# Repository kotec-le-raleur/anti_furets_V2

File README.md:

# anti_furets_V2
##  Anti_furets V2, avec plus de trucs super extra méga cools

* liste des ajouts:
  * un montage plus astucieux pour commander le HP Piézo ( genre de push-pull)
  * un opto-coupleur et triac  8A pour commander une grosse lampe ( coupure au zéro secteur avec un MOC3041)
  * un fusible sur le 12V
  * une carte 80X40 mm faite chez JLCPCB . Le luxe !

Dispositif générateur d'ultra-sons et de flashs lumineux pour effrayer les nuisibles dans un grenier

Ce petit montage trivial , garanti sans NE555, génére des suites aléatoires de sons dans la gamme des 15 à 22 kilo Hertz.   
Des flashs lumineux peuvent être ajoutés avec une ampoule LED 12V ou un ruban de leds.    
On peut aussi mettre un relais pour augmenter la puissance, mais il faudra que la charge et le relais supportent les marche/arret sans griller.   
La consommation sans l'ampoule LED est de 50 mA et une prise murale alim 12V suffit largement !   
Si une diode zéner est utilisée à la place du régulateur, vérifier que la tension à ses bornes ne dépasse pas 5V avant de plugger le µcontrôleur. 

Il faut penser à installer le core ATTiny85 qui implémente la fonction Tone() avant de compiler/télécharger le programme Ajouter dans le menu de l'IDE Arduino la ligne : http://drazzy.com/package_drazzy.com_index.json

Test en vrai: j'ai deux montages comme celui-là dans mon grenier depuis 2 ans !  
il faut bien le placer dans le chemin emprunté par les furets (ou fouines )  
J'ai ajouté des cubes de déodorants pour WC dans les passages et deux diffuseurs ambi-pur océan  (les plus puants )  
Ces saloperies de bestioles se sont barrés pour l'instant , mais la guerre contibue ....  
Bientôt les pièges électriques et mortels !  

A suivre

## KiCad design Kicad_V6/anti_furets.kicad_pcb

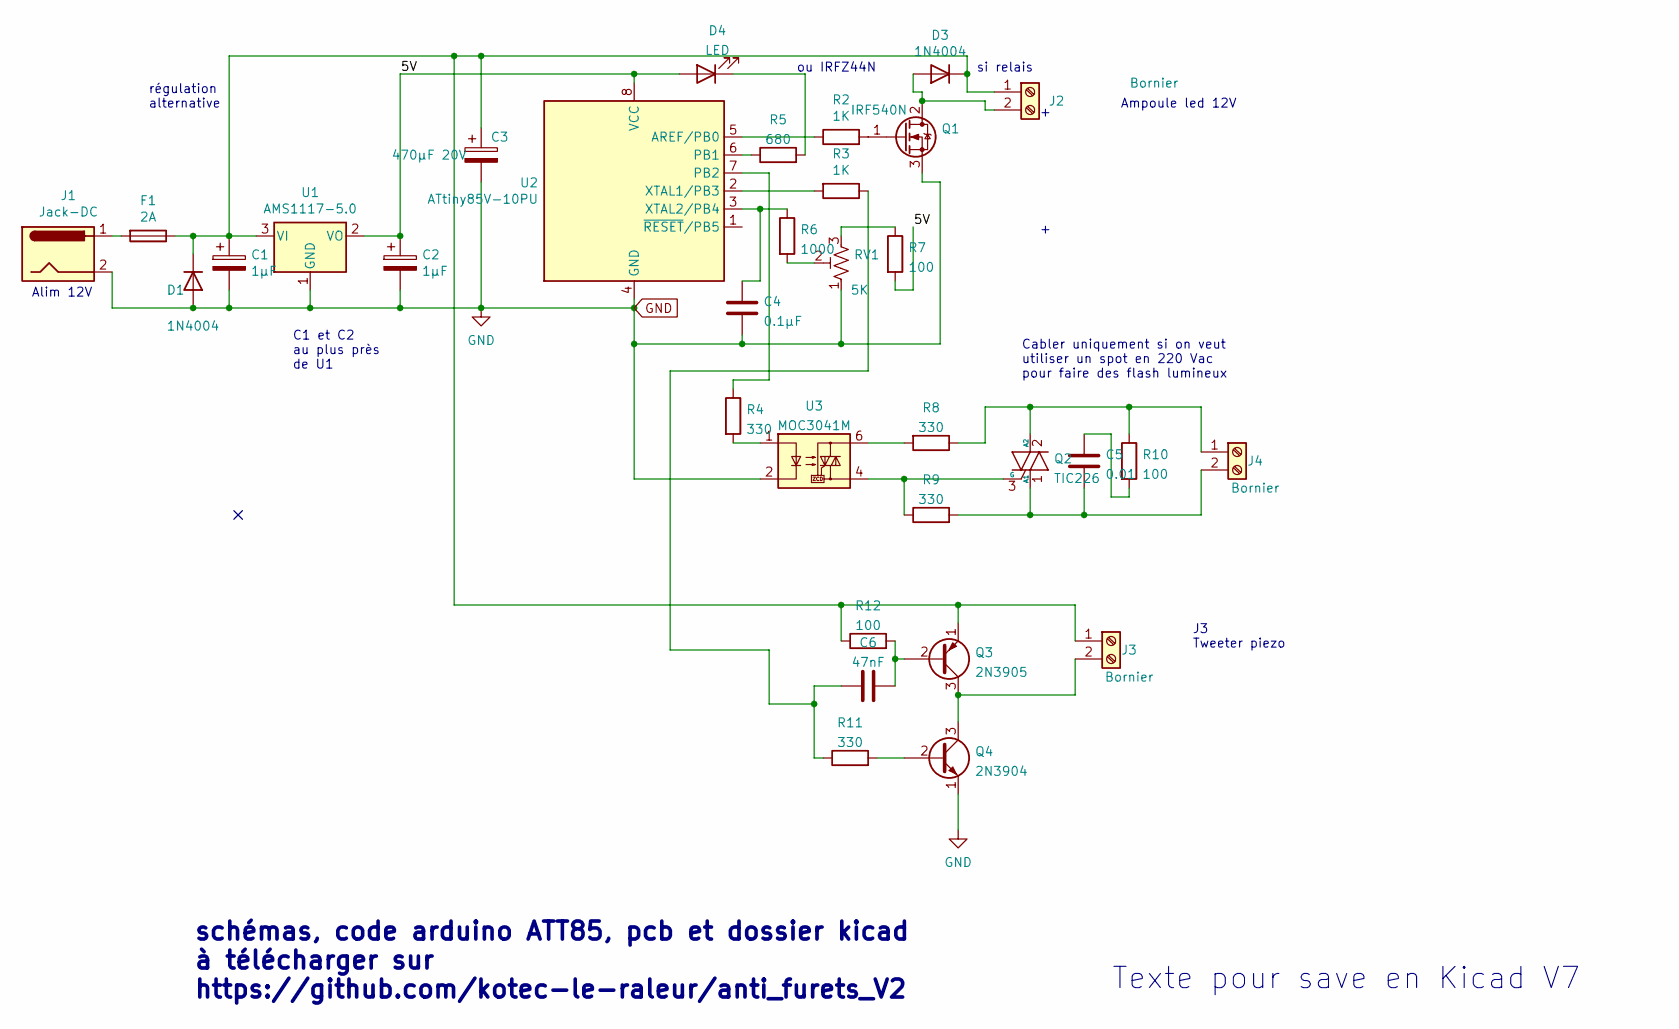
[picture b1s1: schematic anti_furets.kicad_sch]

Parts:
C1, C2: 1µF; C_1206_3216Metric_Pad1.33x1.80mm_HandSolder
C3: 470µF 20V; CP_Radial_D10.0mm_P5.00mm
C4: 0.1µF; C_1210_3225Metric_Pad1.33x2.70mm_HandSolder
C5: 0.01; C_Rect_L7.0mm_W2.0mm_P5.00mm
C6: 47nF; C_Rect_L7.0mm_W2.0mm_P5.00mm
D1, D3: 1N4004; D_DO-41_SOD81_P10.16mm_Horizontal
D4: LED; LED_2010_5025Metric_Pad1.52x2.65mm_HandSolder
F1: 2A; Fuseholder_Littelfuse_445_030_series_5x20mm
J1: Jack-DC; BarrelJack_Wuerth_6941xx301002
J2, J3, J4: Bornier; PinHeader_1x03_P2.54mm_Vertical
Q1: IRF540N; TO-220-3_Vertical
Q2: TIC226; TO-220-3_Vertical
Q3: 2N3905; TO-92_Inline
Q4: 2N3904; TO-92_Inline
R2, R3: 1K; R_0805_2012Metric_Pad1.20x1.40mm_HandSolder
R4, R11: 330; R_0805_2012Metric_Pad1.20x1.40mm_HandSolder
R5: 680; R_0805_2012Metric_Pad1.20x1.40mm_HandSolder
R6: 1000; R_0805_2012Metric_Pad1.20x1.40mm_HandSolder
R7, R12: 100; R_0805_2012Metric_Pad1.20x1.40mm_HandSolder
R8, R9: 330; R_Axial_DIN0207_L6.3mm_D2.5mm_P10.16mm_Horizontal
R10: 100; R_Axial_DIN0207_L6.3mm_D2.5mm_P10.16mm_Horizontal
RV1: 5K; Potentiometer_ACP_CA9-H3,8_Horizontal
U1: AMS1117-5.0; SOT-223-3_TabPin2
U2: ATtiny85V-10PU; DIP-8_W10.16mm_LongPads
U3: MOC3041M; DIP-6_W10.16mm_LongPads

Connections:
/5V: C2.1, D4.2 (A), R7.2, U1.2 (VO), U2.8 (VCC)
GND: C1.2, C2.2, C3.2, C4.2, D1.2 (A), J1.2, Q1.3 (S), Q4.1 (E), RV1.1, U1.1 (GND), U2.4 (GND), U3.2
unnamed: C1.1, C3.1, D1.1 (K), D3.1 (K), F1.1, J2.1, J3.1, Q3.1 (E), R12.1, U1.3 (VI)
unnamed: C4.1, R6.1, U2.3 (XTAL2/PB4)
unnamed: C5.1, R10.2
unnamed: C5.2, J4.2, J4.3, Q2.1 (A1), R9.2
unnamed: C6.1, R3.1, R11.1
unnamed: C6.2, Q3.2 (B), R12.2
unnamed: D3.2 (A), J2.2, J2.3, Q1.2 (D)
unnamed: D4.1 (K), R5.2
unnamed: F1.2, J1.1
unnamed: J3.2, J3.3, Q3.3 (C), Q4.3 (C)
unnamed: J4.1, Q2.2 (A2), R8.1, R10.1
unnamed: Q1.1 (G), R2.2
unnamed: Q2.3 (G), R9.1, U3.4
unnamed: Q4.2 (B), R11.2
unnamed: R2.1, U2.5 (AREF/PB0)
unnamed: R3.2, U2.2 (XTAL1/PB3)
unnamed: R4.1, U2.7 (PB2)
unnamed: R4.2, U3.1
unnamed: R5.1, U2.6 (PB1)
unnamed: R6.2, RV1.2
unnamed: R7.1, RV1.3
unnamed: R8.2, U3.6

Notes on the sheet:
Alim 12V
C1 et C2 au plus près de U1
Cabler uniquement si on veut utiliser un spot en 220 Vac pour faire des flash lumineux
schémas, code arduino ATT85, pcb et dossier kicad à télécharger sur https://github.com/kotec-le-raleur/anti_furets_V2
si relais
ou IRFZ44N
Texte pour save en Kicad V7
régulation alternative
J3 Tweeter piezo
Ampoule led 12V

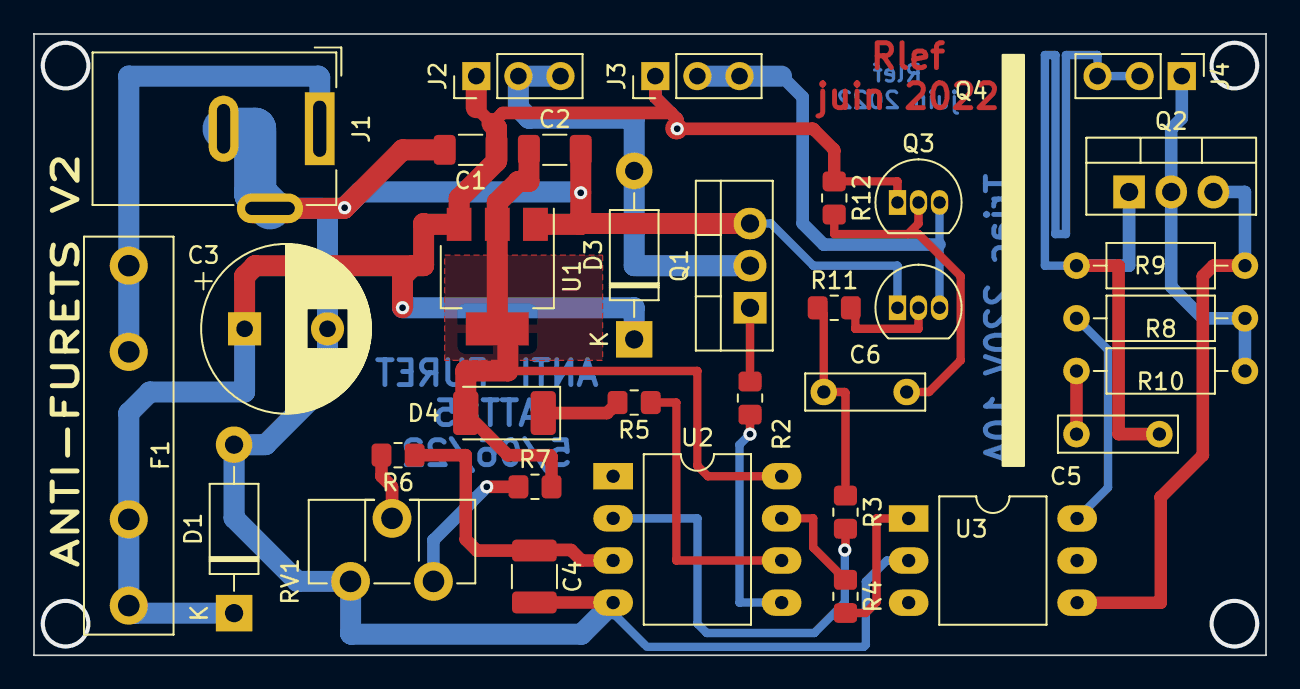
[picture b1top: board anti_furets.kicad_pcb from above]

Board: 2 copper layers, 74.3 x 37.5 mm, 33 parts (0 on the bottom side), 24 nets.

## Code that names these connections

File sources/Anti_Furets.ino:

//  René Lefebvre 6 decembre 2020

// programme chasse_furet
// Pour éloigner cette merde qui squatte le grenier (et qui chie partout)
// Un bon paquet d'ultra-son entre 13 kHz et 18 kHz (à la louche)
// en mode rafale aléatoire
// plus des flashs lumineux aléatoires eux aussi

// ATTENTION  la fonction tone() ne fonctionne pas avec tous les cores att85
// il faut installer le core suivant: http://drazzy.com/package_drazzy.com_index.json
//
// PINS    ATT85
//        ________U_______
//        | 1:RST  8: Vcc |
//        | 2:PB3  7: PB2 | 
//        | 3:PB4  6: PB1 | 
//        | 4:Gnd  5: PB0 | 
//        -----------------


  
    // PB5----pin 1 0 pin 8----Vcc
// A3  PB3----pin 2   pin 7----PB2 A1
// A2  PB4----pin 3   pin 6----PB1
    // Gnd----pin 4   pin 5----PB0
 
//  la tension lue sur A3 est convertie en valeur entre 0 et 1023
//  on multiple par 15 et cela sert de minimum pour la fréquence
//  quand on n'entend plus rien c'est que on est au choix : 
//					sourd, 
//					agé de plus de 60 ans, 
//					ou dans la gamme des ultra sons !
//
// mes chats ont bougé la tête à 20 m du HP, donc , ça fonctionne 
 
 
#define OUT_PIN PB4     // pin 3    vers la gate du 2N7000 pour le HP
#define AJUST_PIN PB3   // pin 2	vers le curseur du potentiometre  0..5V
#define LAMPE_PIN PB0   // pin 5    vers la gate du  IRFZ44 pour le spot

#define NB_FREQ 25

// les fréquences à zéro allument le spot lumineux
int Tab_FREQ[NB_FREQ]  = {100,200,345,0,550,700,850,0,952,1050,1250,1777,
                          1954,0,2154,2500,2750,3000,3300,0,3700,4050,4500,4990,0};
						  
int Tab_SILENCE[10]    = {20,50,80,100,250,300,450,500,750,800};
int Base = 10;     // Initialisation

//*******************  MAIN   *********************
void setup() {
  pinMode(OUT_PIN, OUTPUT);
  pinMode(LAMPE_PIN, OUTPUT);
 //Initialisation du random avec la clé universelle
  randomSeed(42);     
}

//*******************  LOOP   *********************
void loop() {
int i=0;
long frq, tp;
for (i=0;i<10;i++)
    {
	Base = analogRead(AJUST_PIN) * 15;
    frq  = random(NB_FREQ);
    tp   = random(10);
	if (Tab_FREQ[frq] > 0)
	    {
        tone(OUT_PIN, Tab_FREQ[frq]+ Base );
        delay(Tab_SILENCE[tp]);
        // noTone();
        }
	  else				// fréquence = 0 : on allume le spot
		{
        tone(OUT_PIN, Tab_FREQ[frq-1]+ Base );
		digitalWrite(LAMPE_PIN,HIGH);  
	    delay(Tab_SILENCE[tp]+100);
		digitalWrite(LAMPE_PIN,LOW);  
	    //  noTone();
		}
   }
}
//  
// Rien de plus pour ce code trivial
   

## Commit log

2022-06-06 Create Sources
2024-03-14 Create Kicad 7
